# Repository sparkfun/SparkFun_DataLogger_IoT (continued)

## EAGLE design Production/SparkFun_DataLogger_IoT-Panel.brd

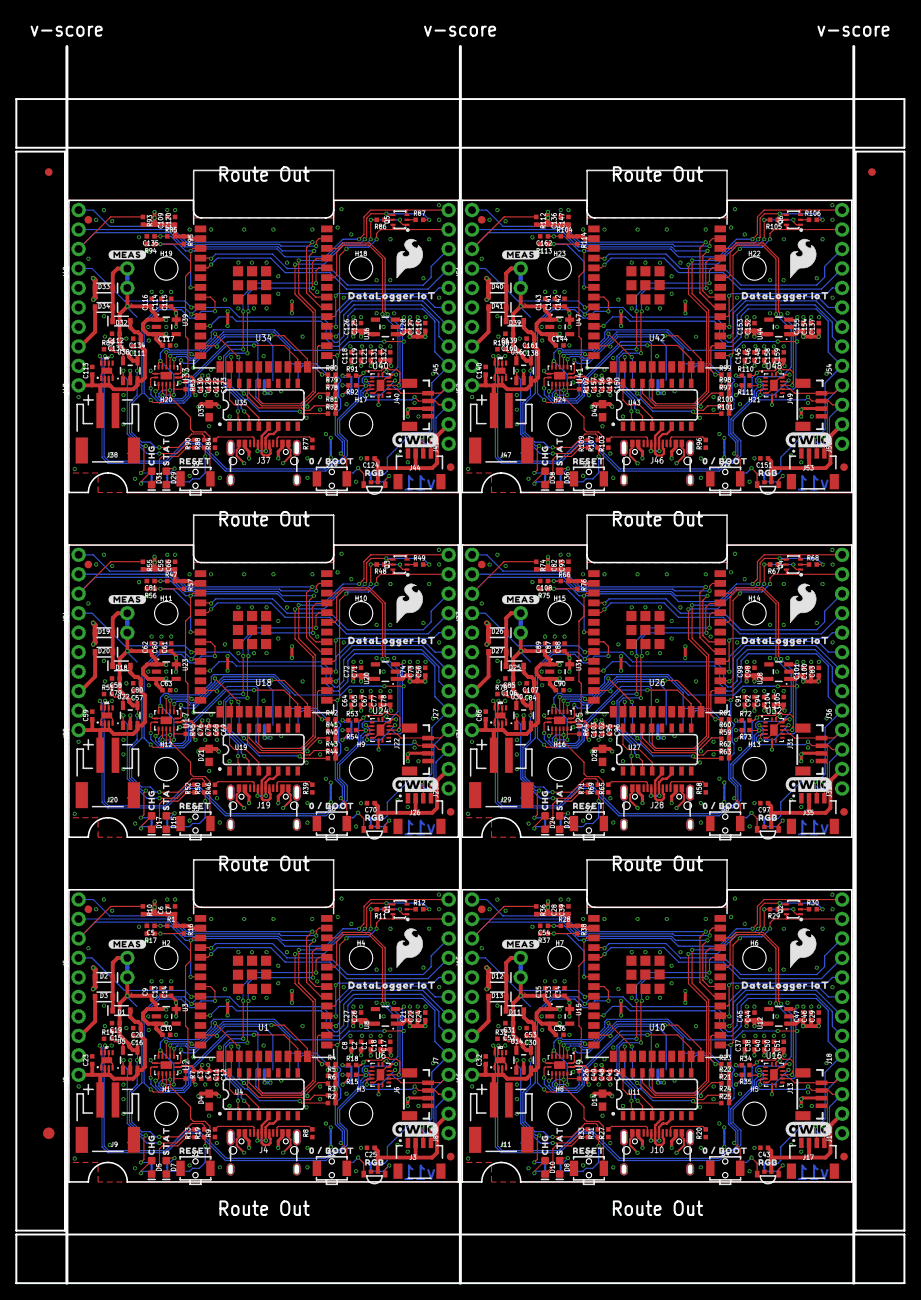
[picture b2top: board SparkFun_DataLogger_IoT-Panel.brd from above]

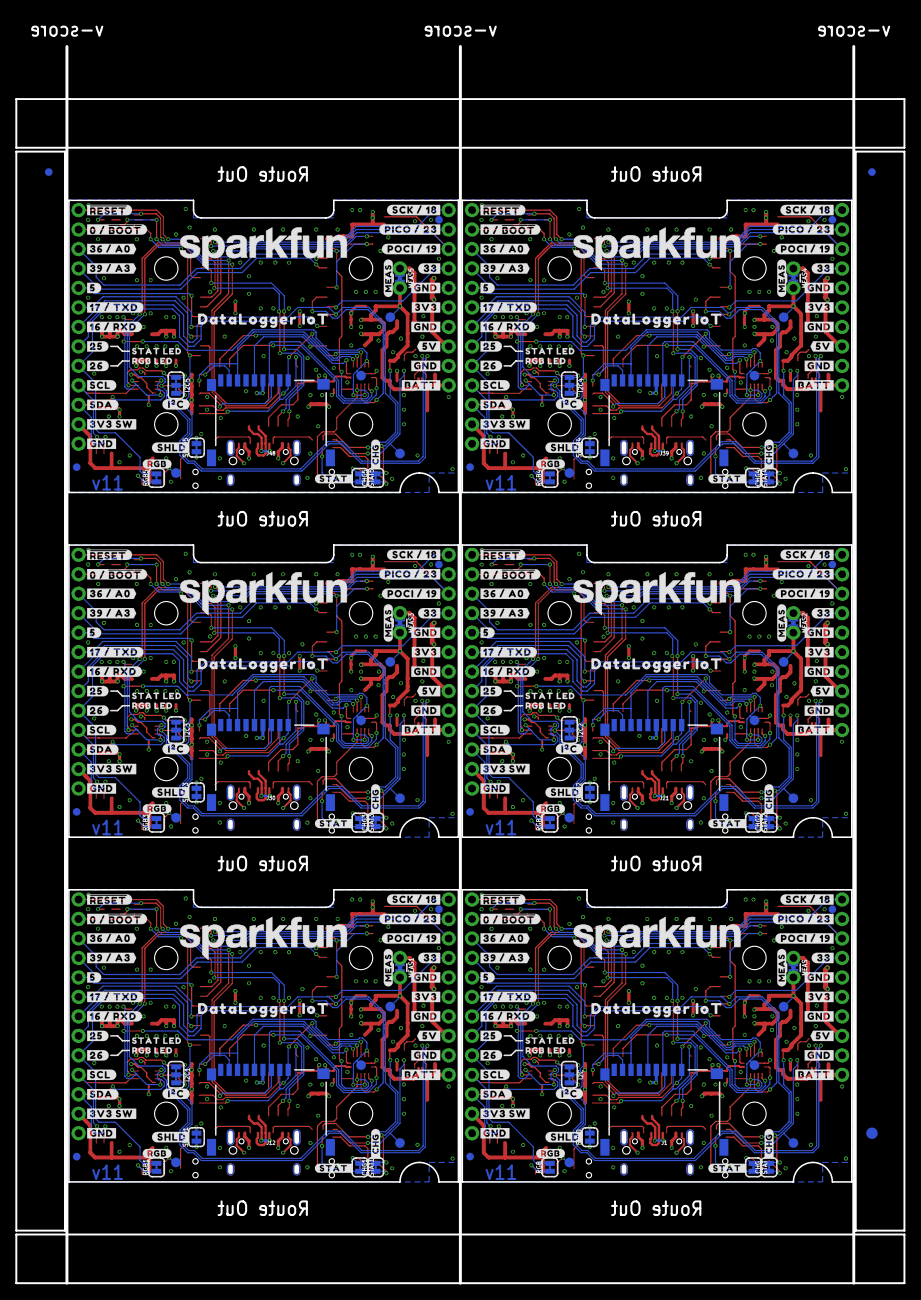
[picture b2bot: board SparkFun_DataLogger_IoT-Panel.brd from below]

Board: 4 copper layers, 115.5 x 164.9 mm, 810 parts (285 on the bottom side), 348 nets.

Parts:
C1, C3, C4, C6, C8, C9, C11, C13, C15, C16, C17, C18, C19, C20, C21, C22, C24, C25, C26, C28, C29, C30, C31, C33, C35, C37, C40, C41, C43, C44, C46, C47, C48, C49, C50, C51, C52, C53, C55, C56, C57, C58, C60, C62, C64, C67, C68, C70, C71, C73, C74, C75, C76, C77, C78, C79, C80, C82, C83, C84, C85, C87, C89, C91, C94, C95, C97, C98, C100, C101, C102, C103, C104, C105, C106, C107, C109, C110, C111, C112, C114, C116, C118, C121, C122, C124, C125, C127, C128, C129, C130, C131, C132, C133, C134, C136, C137, C138, C139, C141, C143, C145, C148, C149, C151, C152, C154, C155, C156, C157, C158, C159, C160, C161: 2.2uF; 0402-TIGHT
C2, C5, C7, C10, C14, C23, C27, C32, C34, C36, C38, C39, C45, C54, C59, C61, C63, C65, C66, C72, C81, C86, C88, C90, C92, C93, C99, C108, C113, C115, C117, C119, C120, C126, C135, C140, C142, C144, C146, C147, C153, C162: 0.1uF; 0402-TIGHT
C12, C42, C69, C96, C123, C150: 10nF; 0402-TIGHT
CHG, CHG1, CHG2, CHG3, CHG4, CHG5: JUMPER-SMT_2_NC_TRACE_SILK; SMT-JUMPER_2_NC_TRACE_SILK
D1, D2, D3, D11, D12, D13, D18, D19, D20, D25, D26, D27, D32, D33, D34, D39, D40, D41: 3A/10V/280mV; SOD-323
D4, D14, D21, D28, D35, D42: TVS; 0603
D5, D10, D17, D24, D31, D38: Yellow; LED-0603
D6, D9, D16, D23, D30, D37: B3DQ3BRG
D7, D8, D15, D22, D29, D36: BLUE; LED-0603
E$1, E$2, E$3, E$4: FIDUCIAL-1X2
E$5, E$6: FIDUCIAL-1.5X3
FD1, FD2, FD3, FD4, FD5, FD6, FD7, FD8, FD9, FD10, FD11, FD12, FD13, FD14, FD15, FD16, FD17, FD18, FD19, FD20, FD21, FD22, FD23, FD24: FIDUCIAL1X2; FIDUCIAL-1X2
H1, H2, H3, H4, H5, H6, H7, H8, H9, H10, H11, H12, H13, H14, H15, H16, H17, H18, H19, H20, H21, H22, H23, H24: STAND-OFFTIGHT; STAND-OFF-TIGHT
I2C, I2C1, I2C2, I2C3, I2C4, I2C5: JUMPER-SMT_3_2-NC_TRACE_SILK; SMT-JUMPER_3_2-NC_TRACE_SILK
J1, J12, J21, J30, J39, J48: MICRO-SD-PUSH-PUSH-EXT-PIN; MICROSD-EXTERNALPIN
J2, J16, J25, J34, J43, J52: 1X06_NO_SILK
J3, J17, J26, J35, J44, J53: QWIIC_RIGHT_ANGLE; JST04_1MM_RA
J4, J10, J19, J28, J37, J46: USB-C-16P_4LAYER-PADS
J5, J8, J14, J15, J23, J24, J32, J33, J41, J42, J50, J51: 1X04_NO_SILK
J6, J13, J22, J31, J40, J49: Vertical Qwiic Connector; JST04_1MM_VERT
J7, J18, J27, J36, J45, J54: 1X09_NO_SILK
J9, J11, J20, J29, J38, J47: JST-2-SMD
LOGO1, LOGO5, LOGO8, LOGO11, LOGO14, LOGO17: SFE_LOGO_NAME.2_INCH; SFE_LOGO_NAME_.2
LOGO2, LOGO6, LOGO9, LOGO12, LOGO15, LOGO18: SFE_LOGO_FLAME.2_INCH; SFE_LOGO_FLAME_.2
LOGO3, LOGO4, LOGO7, LOGO10, LOGO13, LOGO16: QWIIC_LOGO_6MM; QWIIC_6MM
MEAS, MEAS1, MEAS2, MEAS3, MEAS4, MEAS5: JUMPER-COMBO_2_NC_TRACE; COMBO-JUMPER_2_NC_TRACE
Q1, Q2, Q3, Q4, Q5, Q6: SC70-6
R1, R2, R3, R4, R5, R6, R7, R10, R11, R12, R21, R22, R23, R24, R25, R26, R28, R29, R30, R36, R40, R41, R42, R43, R44, R45, R47, R48, R49, R55, R59, R60, R61, R62, R63, R64, R66, R67, R68, R74, R78, R79, R80, R81, R82, R83, R85, R86, R87, R93, R97, R98, R99, R100, R101, R102, R104, R105, R106, R112: 10k; 0402-TIGHT
R8, R9, R20, R27, R39, R46, R58, R65, R77, R84, R96, R103: 5.1k; 0402-TIGHT
R13, R33, R52, R71, R90, R109: 1k; 0402-TIGHT
R14, R32, R51, R70, R89, R108: 2.0K; 0402-TIGHT
R15, R18, R19, R31, R34, R35, R50, R53, R54, R69, R72, R73, R88, R91, R92, R107, R110, R111: 2.2k; 0402-TIGHT
R16, R38, R57, R76, R95, R114: 100k; 0402-TIGHT
R17, R37, R56, R75, R94, R113: 9.1K; 0402-TIGHT
RGB, RGB1, RGB2, RGB3, RGB4, RGB5: JUMPER-SMT_2_NC_TRACE_SILK; SMT-JUMPER_2_NC_TRACE_SILK
S1, S3, S5, S7, S9, S11: RESET; TACTILE_SWITCH_SMD_RIGHT_ANGLE
S2, S4, S6, S8, S10, S12: BOOT; TACTILE_SWITCH_SMD_RIGHT_ANGLE
SHLD, SHLD1, SHLD2, SHLD3, SHLD4, SHLD5: JUMPER-SMT_2_NC_TRACE_SILK; SMT-JUMPER_2_NC_TRACE_SILK
STAT, STAT1, STAT2, STAT3, STAT4, STAT5: JUMPER-SMT_2_NC_TRACE_SILK; SMT-JUMPER_2_NC_TRACE_SILK
TP1, TP2, TP3, TP4, TP5, TP6, TP7, TP8, TP9, TP10, TP11, TP12, TP13, TP14, TP15, TP16, TP17, TP18, TP19, TP20, TP21, TP22, TP23, TP24: TEST-POINT3X5; PAD.03X.05
U1, U10, U18, U26, U34, U42: ESP-WROOM-32E; ESP-WROOM-32D-NARROW
U2, U6, U9, U16, U17, U24, U25, U32, U33, U40, U41, U48: 74HC4066_QUAD_BILATERAL_SWITCH_QFN; 14-QFN
U3, U8, U12, U15, U20, U23, U28, U31, U36, U39, U44, U47: XC6222B331MR-G; SOT23-5
U4, U11, U19, U27, U35, U43: CH340C; SO016
U5, U14, U22, U30, U38, U46: MCP73831; SOT23-5
U7, U13, U21, U29, U37, U45: MAX17048; DFN-8
U$1, U$79, U$119, U$159, U$199, U$239: DATALOGGER_IOT5
U$2, U$15, U$81, U$121, U$161, U$201: RESET0
U$3, U$20, U$82, U$122, U$162, U$202: STAT0
U$4, U$39, U$83, U$123, U$163, U$203: CHG0
U$5, U$72, U$112, U$152, U$192, U$232: #STAT_#0
U$6, U$73, U$113, U$153, U$193, U$233: #RGB#0
U$7, U$70, U$110, U$150, U$190, U$230: 0_#_BOOT0
U$8, U$71, U$111, U$151, U$191, U$231: #_CHG#0
U$9, U$10, U$74, U$75, U$114, U$115, U$154, U$155, U$194, U$195, U$234, U$235: #MEAS#0
U$11, U$76, U$116, U$156, U$196, U$236: RGB0
U$12, U$80, U$120, U$160, U$200, U$240: #5#0
U$13, U$77, U$117, U$157, U$197, U$237: SFE_LOGO_FLAME_STOP_.1
U$14, U$78, U$118, U$158, U$198, U$238: DATALOGGER_IOT2
U$16, U$40, U$84, U$124, U$164, U$204: ##RESET##0
U$17, U$41, U$85, U$125, U$165, U$205: #0_#_#BOOT##0
U$18, U$42, U$86, U$126, U$166, U$206: #36_#_A0#0
U$19, U$43, U$87, U$127, U$167, U$207: #39_#_A3#0
U$21, U$44, U$88, U$128, U$168, U$208: #17_#_TXD#0
U$22, U$49, U$89, U$129, U$169, U$209: #16_#_RXD#0
U$23, U$50, U$90, U$130, U$170, U$210: #25#0
U$24, U$51, U$91, U$131, U$171, U$211: #26#0
U$25, U$52, U$92, U$132, U$172, U$212: #SCL#0
U$26, U$53, U$93, U$133, U$173, U$213: #SDA#0
U$27, U$54, U$94, U$134, U$174, U$214: #3V3_SW#0
U$28, U$55, U$95, U$135, U$175, U$215: #GND#0
U$29, U$30, U$31, U$56, U$57, U$58, U$96, U$97, U$98, U$136, U$137, U$138, U$176, U$177, U$178, U$216, U$217, U$218: #GND#1
U$32, U$59, U$99, U$139, U$179, U$219: #BATT#0
U$33, U$60, U$100, U$140, U$180, U$220: #5V#0
U$34, U$61, U$101, U$141, U$181, U$221: #3V3#0
U$35, U$62, U$102, U$142, U$182, U$222: #33#0
U$36, U$63, U$103, U$143, U$183, U$223: #POCI_#_19#0
U$37, U$64, U$104, U$144, U$184, U$224: #PICO_#_23#0
U$38, U$65, U$105, U$145, U$185, U$225: #SCK_#_18#0
U$45, U$66, U$106, U$146, U$186, U$226: #SHLD#0
U$46, U$67, U$107, U$147, U$187, U$227: #I�C#0
U$47, U$68, U$108, U$148, U$188, U$228: STAT_LED0
U$48, U$69, U$109, U$149, U$189, U$229: RGB_LED0

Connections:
3.3V: C3.1, C4.1, C6.1, C7.1, C11.1, C12.1, C13.1, C14.1, C17.1, C18.1, I2C.2, J2.5, R1.2, R10.2, R16.1, U1.2, U2.14, U3.5, U4.4, U4.16, U6.14
3.3V1: C28.1, C33.1, C34.1, C39.1, C41.1, C42.1, C48.1, C49.1, C50.1, C51.1, I2C1.2, J16.5, R28.2, R36.2, R38.1, U9.14, U10.2, U11.4, U11.16, U15.5, U16.14
3.3V2: C55.1, C60.1, C61.1, C66.1, C68.1, C69.1, C75.1, C76.1, C77.1, C78.1, I2C2.2, J25.5, R47.2, R55.2, R57.1, U17.14, U18.2, U19.4, U19.16, U23.5, U24.14
3.3V3: C82.1, C87.1, C88.1, C93.1, C95.1, C96.1, C102.1, C103.1, C104.1, C105.1, I2C3.2, J34.5, R66.2, R74.2, R76.1, U25.14, U26.2, U27.4, U27.16, U31.5, U32.14
3.3V4: C109.1, C114.1, C115.1, C120.1, C122.1, C123.1, C129.1, C130.1, C131.1, C132.1, I2C4.2, J43.5, R85.2, R93.2, R95.1, U33.14, U34.2, U35.4, U35.16, U39.5, U40.14
3.3V5: C136.1, C141.1, C142.1, C147.1, C149.1, C150.1, C156.1, C157.1, C158.1, C159.1, I2C5.2, J52.5, R104.2, R112.2, R114.1, U41.14, U42.2, U43.4, U43.16, U47.5, U48.14
3.3V_SW: C1.1, C2.1, C8.1, C25.1, C26.1, C27.1, D6.2, J1.4, J3.2, J6.2, J8.2, R2.2, R3.2, R4.2, R5.2, R6.2, U8.5
3.3V_SW1: C37.1, C38.1, C40.1, C43.1, C44.1, C45.1, D9.2, J12.4, J13.2, J14.2, J17.2, R21.2, R22.2, R23.2, R24.2, R25.2, U12.5
3.3V_SW2: C64.1, C65.1, C67.1, C70.1, C71.1, C72.1, D16.2, J21.4, J22.2, J23.2, J26.2, R40.2, R41.2, R42.2, R43.2, R44.2, U20.5
3.3V_SW3: C91.1, C92.1, C94.1, C97.1, C98.1, C99.1, D23.2, J30.4, J31.2, J32.2, J35.2, R59.2, R60.2, R61.2, R62.2, R63.2, U28.5
3.3V_SW4: C118.1, C119.1, C121.1, C124.1, C125.1, C126.1, D30.2, J39.4, J40.2, J41.2, J44.2, R78.2, R79.2, R80.2, R81.2, R82.2, U36.5
3.3V_SW5: C145.1, C146.1, C148.1, C151.1, C152.1, C153.1, D37.2, J48.4, J49.2, J50.2, J53.2, R97.2, R98.2, R99.2, R100.2, R101.2, U44.5
5V: D3.A, J2.3
5V1: D13.A, J16.3
5V2: D20.A, J25.3
5V3: D27.A, J34.3
5V4: D34.A, J43.3
5V5: D41.A, J52.3
!RESET!: C5.1, J7.9, Q1.3, R1.1, S1.2, U1.3, U2.12
!RESET!1: C54.1, J18.9, Q2.3, R28.1, S3.2, U9.12, U10.3
!RESET!2: C81.1, J27.9, Q3.3, R47.1, S5.2, U17.12, U18.3
!RESET!3: C108.1, J36.9, Q4.3, R66.1, S7.2, U25.12, U26.3
!RESET!4: C135.1, J45.9, Q5.3, R85.1, S9.2, U33.12, U34.3
!RESET!5: C162.1, J54.9, Q6.3, R104.1, S11.2, U41.12, U42.3
CH340-DTR: Q1.1, R11.2, U4.13
CH340-DTR1: Q2.1, R29.2, U11.13
CH340-DTR2: Q3.1, R48.2, U19.13
CH340-DTR3: Q4.1, R67.2, U27.13
CH340-DTR4: Q5.1, R86.2, U35.13
CH340-DTR5: Q6.1, R105.2, U43.13
CH340-RTS: Q1.4, R12.2, U4.14
CH340-RTS1: Q2.4, R30.2, U11.14
CH340-RTS2: Q3.4, R49.2, U19.14
CH340-RTS3: Q4.4, R68.2, U27.14
CH340-RTS4: Q5.4, R87.2, U35.14
CH340-RTS5: Q6.4, R106.2, U43.14
CH340-RX: U1.35, U4.3
CH340-RX1: U10.35, U11.3
CH340-RX2: U18.35, U19.3
CH340-RX3: U26.35, U27.3
CH340-RX4: U34.35, U35.3
CH340-RX5: U42.35, U43.3
CH340-TX: U1.34, U4.2
CH340-TX1: U10.34, U11.2
CH340-TX2: U18.34, U19.2
CH340-TX3: U26.34, U27.2
CH340-TX4: U34.34, U35.2
CH340-TX5: U42.34, U43.2
D+: J4.A6, J4.B6, U4.5
D+1: J10.A6, J10.B6, U11.5
D+2: J19.A6, J19.B6, U19.5
D+3: J28.A6, J28.B6, U27.5
D+4: J37.A6, J37.B6, U35.5
D+5: J46.A6, J46.B6, U43.5
D-: J4.A7, J4.B7, U4.6
D-1: J10.A7, J10.B7, U11.6
D-2: J19.A7, J19.B7, U19.6
D-3: J28.A7, J28.B7, U27.6
D-4: J37.A7, J37.B7, U35.6
D-5: J46.A7, J46.B7, U43.6
ESP0/!BOOT!: J7.8, Q1.6, S2.2, U1.25
ESP0/!BOOT!1: J18.8, Q2.6, S4.2, U10.25
ESP0/!BOOT!2: J27.8, Q3.6, S6.2, U18.25
ESP0/!BOOT!3: J36.8, Q4.6, S8.2, U26.25
ESP0/!BOOT!4: J45.8, Q5.6, S10.2, U34.25
ESP0/!BOOT!5: J54.8, Q6.6, S12.2, U42.25
ESP1: J15.1, U10.9
ESP2: J18.5, U10.29
ESP2/DAT0: U1.24, U2.1
ESP2/DAT1: U9.1, U10.24
ESP2/DAT2: U17.1, U18.24
ESP2/DAT3: U25.1, U26.24
ESP2/DAT4: U33.1, U34.24
ESP2/DAT5: U41.1, U42.24
ESP3: J24.1, U18.9
ESP4: J27.5, U18.29
ESP4/DAT1: J1.8, R4.1, U1.26
ESP4/DAT2: J12.8, R23.1, U10.26
ESP4/DAT3: J21.8, R42.1, U18.26
ESP4/DAT4: J30.8, R61.1, U26.26
ESP4/DAT5: J39.8, R80.1, U34.26
ESP4/DAT6: J48.8, R99.1, U42.26
ESP5: J7.5, U1.29
ESP6: J33.1, U26.9
ESP7: J36.5, U26.29
ESP8: J42.1, U34.9
ESP9: J45.5, U34.29
ESP10: J51.1, U42.9
ESP11: J54.5, U42.29
ESP12/DAT1: U9.4, U10.14
ESP12/DAT2: U1.14, U2.4
ESP12/DAT3: U17.4, U18.14
ESP12/DAT4: U25.4, U26.14
ESP12/DAT5: U33.4, U34.14
ESP12/DAT6: U41.4, U42.14
ESP13/DAT1: J12.2, R25.1, U10.16
ESP13/DAT2: J21.2, R44.1, U18.16
ESP13/DAT3: J1.2, R2.1, U1.16
ESP13/DAT4: J30.2, R63.1, U26.16
ESP13/DAT5: J39.2, R82.1, U34.16
ESP13/DAT6: J48.2, R101.1, U42.16
ESP14/CLK: J1.5, U1.13
ESP14/CLK1: J12.5, U10.13
ESP14/CLK2: J21.5, U18.13
ESP14/CLK3: J30.5, U26.13
ESP14/CLK4: J39.5, U34.13
ESP14/CLK5: J48.5, U42.13
ESP15/CMD: U1.23, U2.8
ESP15/CMD1: U9.8, U10.23
ESP15/CMD2: U17.8, U18.23
ESP15/CMD3: U25.8, U26.23
ESP15/CMD4: U33.8, U34.23
ESP15/CMD5: U41.8, U42.23
ESP16/RXD: J7.3, U1.27
ESP16/RXD1: J18.3, U10.27
ESP16/RXD2: J27.3, U18.27
ESP16/RXD3: J36.3, U26.27
ESP16/RXD4: J45.3, U34.27
ESP16/RXD5: J54.3, U42.27
ESP17/TXD: J7.4, U1.28
ESP17/TXD1: J18.4, U10.28
ESP17/TXD2: J27.4, U18.28
ESP17/TXD3: J36.4, U26.28
ESP17/TXD4: J45.4, U34.28
ESP17/TXD5: J54.4, U42.28
ESP18/SCK: J5.4, U1.30
ESP18/SCK1: J15.4, U10.30
ESP18/SCK2: J24.4, U18.30
ESP18/SCK3: J33.4, U26.30
ESP18/SCK4: J42.4, U34.30
ESP18/SCK5: J51.4, U42.30
ESP19/POCI: J5.2, R10.1, U1.31
ESP19/POCI1: J15.2, R36.1, U10.31
ESP19/POCI2: J24.2, R55.1, U18.31
ESP19/POCI3: J33.2, R74.1, U26.31
ESP19/POCI4: J42.2, R93.1, U34.31
ESP19/POCI5: J51.2, R112.1, U42.31
ESP21/SDA: R15.1, U1.33, U6.4, U7.8
ESP21/SDA1: R35.1, U10.33, U13.8, U16.4
ESP21/SDA2: R54.1, U18.33, U21.8, U24.4
ESP21/SDA3: R73.1, U26.33, U29.8, U32.4
ESP21/SDA4: R92.1, U34.33, U37.8, U40.4
ESP21/SDA5: R111.1, U42.33, U45.8, U48.4
ESP22/SCL: R18.2, U1.36, U6.11, U7.7
ESP22/SCL1: R34.2, U10.36, U13.7, U16.11
ESP22/SCL2: R53.2, U18.36, U21.7, U24.11
ESP22/SCL3: R72.2, U26.36, U29.7, U32.11
ESP22/SCL4: R91.2, U34.36, U37.7, U40.11
ESP22/SCL5: R110.2, U42.36, U45.7, U48.11
ESP23/PICO: J5.3, U1.37
ESP23/PICO1: J15.3, U10.37
ESP23/PICO2: J24.3, U18.37
ESP23/PICO3: J33.3, U26.37
ESP23/PICO4: J42.3, U34.37
ESP23/PICO5: J51.3, U42.37
ESP25/LED: J7.2, R19.2, U1.10
ESP25/LED1: J18.2, R31.2, U10.10
ESP25/LED2: J27.2, R50.2, U18.10
ESP25/LED3: J36.2, R69.2, U26.10
ESP25/LED4: J45.2, R88.2, U34.10
ESP25/LED5: J54.2, R107.2, U42.10
ESP26/RGBLED: J7.1, RGB.2, U1.11
ESP26/RGBLED1: J18.1, RGB1.2, U10.11
ESP26/RGBLED2: J27.1, RGB2.2, U18.11
ESP26/RGBLED3: J36.1, RGB3.2, U26.11
ESP26/RGBLED4: J45.1, RGB4.2, U34.11
ESP26/RGBLED5: J54.1, RGB5.2, U42.11
ESP32/PWREN: U1.8, U2.11
ESP32/PWREN1: U9.11, U10.8
ESP32/PWREN2: U17.11, U18.8
ESP32/PWREN3: U25.11, U26.8
ESP32/PWREN4: U33.11, U34.8
ESP32/PWREN5: U41.11, U42.8
ESP33: J5.1, U1.9
ESP35/A1: R37.1, R38.2, U10.7
ESP35/A2: R56.1, R57.2, U18.7
ESP35/A3: R75.1, R76.2, U26.7
ESP35/A4: R94.1, R95.2, U34.7
ESP35/A5: R113.1, R114.2, U42.7
ESP35/A7: R16.2, R17.1, U1.7
ESP36/A0: J7.7, U1.4
ESP36/A1: J18.7, U10.4
ESP36/A2: J27.7, U18.4
ESP36/A3: J36.7, U26.4
ESP36/A4: J45.7, U34.4
ESP36/A5: J54.7, U42.4
ESP39/A1: J18.6, U10.5
ESP39/A2: J27.6, U18.5
ESP39/A3: J7.6, U1.5
ESP39/A4: J36.6, U26.5
ESP39/A5: J45.6, U34.5
ESP39/A6: J54.6, U42.5
GND: C1.2, C2.2, C3.2, C4.2, C5.2, C6.2, C7.2, C8.2, C9.2, C10.2, C11.2, C12.2, C13.2, C14.2, C15.2, C16.2, C17.2, C18.2, C19.2, C20.2, C21.2, C22.2, C23.2, C24.2, C25.2, C26.2, C27.2, D4.1, D6.1, D7.C, J1.6, J1.10, J1.11, J1.12, J1.13, J2.2, J2.4, J2.6, J3.1, J4.GND, J4.GND2, J6.1, J8.1, J9.1, R7.1, R8.1, R9.1, R14.1, R17.2, S1.1, S2.1, SHLD.1, U1.1, U1.15, U1.38, U1.GND1, U1.GNDT1, U1.GNDT2, U1.GNDT3, U1.GNDT4, U1.GNDT5, U1.GNDT6, U1.GNDT7, U1.GNDT8, U2.7, U2.EPAD, U3.2, U4.1, U5.2, U6.6, U6.7, U6.13, U6.EPAD, U7.1, U7.4, U7.6, U7.9, U8.2
GND1: C28.2, C29.2, C30.2, C31.2, C32.2, C33.2, C34.2, C35.2, C36.2, C37.2, C38.2, C39.2, C40.2, C41.2, C42.2, C43.2, C44.2, C45.2, C46.2, C47.2, C48.2, C49.2, C50.2, C51.2, C52.2, C53.2, C54.2, D8.C, D9.1, D14.1, J10.GND, J10.GND2, J11.1, J12.6, J12.10, J12.11, J12.12, J12.13, J13.1, J14.1, J16.2, J16.4, J16.6, J17.1, R20.1, R26.1, R27.1, R32.1, R37.2, S3.1, S4.1, SHLD1.1, U9.7, U9.EPAD, U10.1, U10.15, U10.38, U10.GND1, U10.GNDT1, U10.GNDT2, U10.GNDT3, U10.GNDT4, U10.GNDT5, U10.GNDT6, U10.GNDT7, U10.GNDT8, U11.1, U12.2, U13.1, U13.4, U13.6, U13.9, U14.2, U15.2, U16.6, U16.7, U16.13, U16.EPAD
GND2: C55.2, C56.2, C57.2, C58.2, C59.2, C60.2, C61.2, C62.2, C63.2, C64.2, C65.2, C66.2, C67.2, C68.2, C69.2, C70.2, C71.2, C72.2, C73.2, C74.2, C75.2, C76.2, C77.2, C78.2, C79.2, C80.2, C81.2, D15.C, D16.1, D21.1, J19.GND, J19.GND2, J20.1, J21.6, J21.10, J21.11, J21.12, J21.13, J22.1, J23.1, J25.2, J25.4, J25.6, J26.1, R39.1, R45.1, R46.1, R51.1, R56.2, S5.1, S6.1, SHLD2.1, U17.7, U17.EPAD, U18.1, U18.15, U18.38, U18.GND1, U18.GNDT1, U18.GNDT2, U18.GNDT3, U18.GNDT4, U18.GNDT5, U18.GNDT6, U18.GNDT7, U18.GNDT8, U19.1, U20.2, U21.1, U21.4, U21.6, U21.9, U22.2, U23.2, U24.6, U24.7, U24.13, U24.EPAD
GND3: C82.2, C83.2, C84.2, C85.2, C86.2, C87.2, C88.2, C89.2, C90.2, C91.2, C92.2, C93.2, C94.2, C95.2, C96.2, C97.2, C98.2, C99.2, C100.2, C101.2, C102.2, C103.2, C104.2, C105.2, C106.2, C107.2, C108.2, D22.C, D23.1, D28.1, J28.GND, J28.GND2, J29.1, J30.6, J30.10, J30.11, J30.12, J30.13, J31.1, J32.1, J34.2, J34.4, J34.6, J35.1, R58.1, R64.1, R65.1, R70.1, R75.2, S7.1, S8.1, SHLD3.1, U25.7, U25.EPAD, U26.1, U26.15, U26.38, U26.GND1, U26.GNDT1, U26.GNDT2, U26.GNDT3, U26.GNDT4, U26.GNDT5, U26.GNDT6, U26.GNDT7, U26.GNDT8, U27.1, U28.2, U29.1, U29.4, U29.6, U29.9, U30.2, U31.2, U32.6, U32.7, U32.13, U32.EPAD
GND4: C109.2, C110.2, C111.2, C112.2, C113.2, C114.2, C115.2, C116.2, C117.2, C118.2, C119.2, C120.2, C121.2, C122.2, C123.2, C124.2, C125.2, C126.2, C127.2, C128.2, C129.2, C130.2, C131.2, C132.2, C133.2, C134.2, C135.2, D29.C, D30.1, D35.1, J37.GND, J37.GND2, J38.1, J39.6, J39.10, J39.11, J39.12, J39.13, J40.1, J41.1, J43.2, J43.4, J43.6, J44.1, R77.1, R83.1, R84.1, R89.1, R94.2, S9.1, S10.1, SHLD4.1, U33.7, U33.EPAD, U34.1, U34.15, U34.38, U34.GND1, U34.GNDT1, U34.GNDT2, U34.GNDT3, U34.GNDT4, U34.GNDT5, U34.GNDT6, U34.GNDT7, U34.GNDT8, U35.1, U36.2, U37.1, U37.4, U37.6, U37.9, U38.2, U39.2, U40.6, U40.7, U40.13, U40.EPAD
GND5: C136.2, C137.2, C138.2, C139.2, C140.2, C141.2, C142.2, C143.2, C144.2, C145.2, C146.2, C147.2, C148.2, C149.2, C150.2, C151.2, C152.2, C153.2, C154.2, C155.2, C156.2, C157.2, C158.2, C159.2, C160.2, C161.2, C162.2, D36.C, D37.1, D42.1, J46.GND, J46.GND2, J47.1, J48.6, J48.10, J48.11, J48.12, J48.13, J49.1, J50.1, J52.2, J52.4, J52.6, J53.1, R96.1, R102.1, R103.1, R108.1, R113.2, S11.1, S12.1, SHLD5.1, U41.7, U41.EPAD, U42.1, U42.15, U42.38, U42.GND1, U42.GNDT1, U42.GNDT2, U42.GNDT3, U42.GNDT4, U42.GNDT5, U42.GNDT6, U42.GNDT7, U42.GNDT8, U43.1, U44.2, U45.1, U45.4, U45.6, U45.9, U46.2, U47.2, U48.6, U48.7, U48.13, U48.EPAD
unnamed: J4.B5, R8.2
unnamed: J4.A5, R9.2
unnamed: D1.C, D2.C, D3.C, MEAS.1, MEAS.3
unnamed: Q1.2, R12.1
unnamed: Q1.5, R11.1
unnamed: R19.1, STAT.2
unnamed: D6.4, TP1.1
unnamed: CHG.1, D5.A
unnamed: D5.C, R13.1
unnamed: R13.2, TP3.1, U5.1
unnamed: R14.2, U5.5
unnamed: D6.3, RGB.1
unnamed: D7.A, STAT.1
unnamed: J10.B5, R20.2
unnamed: J10.A5, R27.2
unnamed: I2C.1, R18.1
unnamed: I2C.3, R15.2
unnamed: Q2.2, R30.1
unnamed: Q2.5, R29.1
unnamed: D9.4, TP5.1
unnamed: R32.2, U14.5
unnamed: R31.1, STAT1.2
unnamed: D8.A, STAT1.1
unnamed: I2C1.1, R34.1
unnamed: I2C1.3, R35.2
unnamed: CHG1.1, D10.A
unnamed: D10.C, R33.1
unnamed: R33.2, TP8.1, U14.1
unnamed: D9.3, RGB1.1
unnamed: D11.C, D12.C, D13.C, MEAS1.1, MEAS1.3
unnamed: J19.B5, R39.2
unnamed: J19.A5, R46.2
unnamed: Q3.2, R49.1
unnamed: Q3.5, R48.1
unnamed: D16.4, TP9.1
unnamed: R51.2, U22.5
unnamed: R50.1, STAT2.2
unnamed: D15.A, STAT2.1
unnamed: I2C2.1, R53.1
unnamed: I2C2.3, R54.2
unnamed: CHG2.1, D17.A
unnamed: D17.C, R52.1
unnamed: R52.2, TP12.1, U22.1
unnamed: D16.3, RGB2.1
unnamed: D18.C, D19.C, D20.C, MEAS2.1, MEAS2.3
unnamed: J28.B5, R58.2
unnamed: J28.A5, R65.2
unnamed: Q4.2, R68.1
unnamed: Q4.5, R67.1
unnamed: D23.4, TP13.1
unnamed: R70.2, U30.5
unnamed: R69.1, STAT3.2
unnamed: D22.A, STAT3.1
unnamed: I2C3.1, R72.1
unnamed: I2C3.3, R73.2
unnamed: CHG3.1, D24.A
unnamed: D24.C, R71.1
unnamed: R71.2, TP16.1, U30.1
unnamed: D23.3, RGB3.1
unnamed: D25.C, D26.C, D27.C, MEAS3.1, MEAS3.3
unnamed: J37.B5, R77.2
unnamed: J37.A5, R84.2
unnamed: Q5.2, R87.1
unnamed: Q5.5, R86.1
unnamed: D30.4, TP17.1
unnamed: R89.2, U38.5
unnamed: R88.1, STAT4.2
unnamed: D29.A, STAT4.1
unnamed: I2C4.1, R91.1
unnamed: I2C4.3, R92.2
unnamed: CHG4.1, D31.A
unnamed: D31.C, R90.1
unnamed: R90.2, TP20.1, U38.1
unnamed: D30.3, RGB4.1
unnamed: D32.C, D33.C, D34.C, MEAS4.1, MEAS4.3
unnamed: J46.B5, R96.2
unnamed: J46.A5, R103.2
unnamed: Q6.2, R106.1
unnamed: Q6.5, R105.1
unnamed: D37.4, TP21.1
unnamed: R108.2, U46.5
unnamed: R107.1, STAT5.2
unnamed: D36.A, STAT5.1
unnamed: I2C5.1, R110.1
unnamed: I2C5.3, R111.2
unnamed: CHG5.1, D38.A
unnamed: D38.C, R109.1
unnamed: R109.2, TP24.1, U46.1
unnamed: D37.3, RGB5.1
unnamed: D39.C, D40.C, D41.C, MEAS5.1, MEAS5.3
PWREN: R7.2, TP4.1, U2.5, U2.6, U2.10, U2.13, U6.5, U6.12, U8.3
PWREN1: R26.2, TP6.1, U9.5, U9.6, U9.10, U9.13, U12.3, U16.5, U16.12
PWREN2: R45.2, TP10.1, U17.5, U17.6, U17.10, U17.13, U20.3, U24.5, U24.12
PWREN3: R64.2, TP14.1, U25.5, U25.6, U25.10, U25.13, U28.3, U32.5, U32.12
PWREN4: R83.2, TP18.1, U33.5, U33.6, U33.10, U33.13, U36.3, U40.5, U40.12
PWREN5: R102.2, TP22.1, U41.5, U41.6, U41.10, U41.13, U44.3, U48.5, U48.12
QWIIC_SCL: J3.4, J6.4, J8.4, U6.10
QWIIC_SCL1: J13.4, J14.4, J17.4, U16.10
QWIIC_SCL2: J22.4, J23.4, J26.4, U24.10
QWIIC_SCL3: J31.4, J32.4, J35.4, U32.10
QWIIC_SCL4: J40.4, J41.4, J44.4, U40.10
QWIIC_SCL5: J49.4, J50.4, J53.4, U48.10
QWIIC_SDA: J3.3, J6.3, J8.3, U6.3
QWIIC_SDA1: J13.3, J14.3, J17.3, U16.3
QWIIC_SDA2: J22.3, J23.3, J26.3, U24.3
QWIIC_SDA3: J31.3, J32.3, J35.3, U32.3
QWIIC_SDA4: J40.3, J41.3, J44.3, U40.3
QWIIC_SDA5: J49.3, J50.3, J53.3, U48.3
SD_CMD: J1.3, R6.1, U2.9
SD_CMD1: J12.3, R21.1, U9.9
SD_CMD2: J21.3, R40.1, U17.9
SD_CMD3: J30.3, R59.1, U25.9
SD_CMD4: J39.3, R78.1, U33.9
SD_CMD5: J48.3, R97.1, U41.9
SD_DAT0: J1.7, R5.1, U2.2
SD_DAT1: J12.7, R22.1, U9.2
SD_DAT2: J1.1, R3.1, U2.3
SD_DAT3: J12.1, R24.1, U9.3
SD_DAT4: J21.7, R41.1, U17.2
SD_DAT5: J21.1, R43.1, U17.3
SD_DAT6: J30.7, R60.1, U25.2
SD_DAT7: J30.1, R62.1, U25.3
SD_DAT8: J39.7, R79.1, U33.2
SD_DAT9: J39.1, R81.1, U33.3
SD_DAT10: J48.7, R98.1, U41.2
SD_DAT11: J48.1, R100.1, U41.3
SHIELD: J4.SHLD1, J4.SHLD2, J4.SHLD3, J4.SHLD4, SHLD.2
SHIELD1: J10.SHLD1, J10.SHLD2, J10.SHLD3, J10.SHLD4, SHLD1.2
SHIELD2: J19.SHLD1, J19.SHLD2, J19.SHLD3, J19.SHLD4, SHLD2.2
SHIELD3: J28.SHLD1, J28.SHLD2, J28.SHLD3, J28.SHLD4, SHLD3.2
SHIELD4: J37.SHLD1, J37.SHLD2, J37.SHLD3, J37.SHLD4, SHLD4.2
SHIELD5: J46.SHLD1, J46.SHLD2, J46.SHLD3, J46.SHLD4, SHLD5.2
VIN: C9.1, C10.1, C15.1, C19.1, C21.1, C22.1, C24.1, CHG.2, MEAS.2, MEAS.4, TP2.1, U3.1, U3.3, U5.4, U8.1
VIN1: C29.1, C31.1, C35.1, C36.1, C46.1, C47.1, C52.1, CHG1.2, MEAS1.2, MEAS1.4, TP7.1, U12.1, U14.4, U15.1, U15.3
VIN2: C56.1, C58.1, C62.1, C63.1, C73.1, C74.1, C79.1, CHG2.2, MEAS2.2, MEAS2.4, TP11.1, U20.1, U22.4, U23.1, U23.3
VIN3: C83.1, C85.1, C89.1, C90.1, C100.1, C101.1, C106.1, CHG3.2, MEAS3.2, MEAS3.4, TP15.1, U28.1, U30.4, U31.1, U31.3
VIN4: C110.1, C112.1, C116.1, C117.1, C127.1, C128.1, C133.1, CHG4.2, MEAS4.2, MEAS4.4, TP19.1, U36.1, U38.4, U39.1, U39.3
VIN5: C137.1, C139.1, C143.1, C144.1, C154.1, C155.1, C160.1, CHG5.2, MEAS5.2, MEAS5.4, TP23.1, U44.1, U46.4, U47.1, U47.3
V_BATT: C16.1, C20.1, C23.1, D1.A, J2.1, J9.2, U5.3, U7.2, U7.3
V_BATT1: C30.1, C32.1, C53.1, D11.A, J11.2, J16.1, U13.2, U13.3, U14.3
V_BATT2: C57.1, C59.1, C80.1, D18.A, J20.2, J25.1, U21.2, U21.3, U22.3
V_BATT3: C84.1, C86.1, C107.1, D25.A, J29.2, J34.1, U29.2, U29.3, U30.3
V_BATT4: C111.1, C113.1, C134.1, D32.A, J38.2, J43.1, U37.2, U37.3, U38.3
V_BATT5: C138.1, C140.1, C161.1, D39.A, J47.2, J52.1, U45.2, U45.3, U46.3
V_USB: D2.A, D4.2, J4.VBUS1, J4.VBUS2
V_USB1: D12.A, D14.2, J10.VBUS1, J10.VBUS2
V_USB2: D19.A, D21.2, J19.VBUS1, J19.VBUS2
V_USB3: D26.A, D28.2, J28.VBUS1, J28.VBUS2
V_USB4: D33.A, D35.2, J37.VBUS1, J37.VBUS2
V_USB5: D40.A, D42.2, J46.VBUS1, J46.VBUS2

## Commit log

2023-05-03 Remove unused directories.
2023-05-03 Add existing examples.
    Added examples from DataLogger IoT 9DoF.
2023-05-03 Update board for DataLogger IoT
    Remove IMU and associated passives.
    Remove MAG and associated passives.
    Populate C31 with 100n.
    Add MEAS jumper.
    Set PWREN PDR to 10k from 100k.
    Add HW versioning circuit.
2023-05-04 Pre-Design Review updates
    Add 9.1k Res for hardware versioning.
    Move MEAS to be on grid.
    Shuffle diodes around a little.
    Move silk to fill gaps.
    Change LED bias resistor to meet standards.
    Made HW versioning be on A7 to match RTK designs.
2023-05-04 Added Panelization files.
2023-05-05 Post design review updates.
    Change BO silk for D5.
    Remove unused PURs.
    Clean up wire stubs.
    Remove GND guard trace.
    Add GND vias near switching vias.
    Renumber Schematic.
2023-05-11 Added Fuel Gauge I2C address.
2023-07-11 Update for v11 PCB
    Removed OSHW logo.
2023-07-17 Condensed Schematic.
2023-07-18 NP unused resistors
2023-07-19 Update VREG
2023-09-06 Update Hardware Tests
    - Update References for DataLogger IoT by Removing 9DoF References
    - Update with Paul's warnings
2023-09-06 Delete enclosure folder.
    Unused.
2023-09-06 Restructure HW Tests
    Removed IMU/MAG tests. Renamed other tests for ordering. Removed unnecessary sections of kept tests. Removed redundant deep sleep example.
